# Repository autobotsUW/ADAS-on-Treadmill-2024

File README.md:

# ADAS-on-Treadmill-2024

## The project
The University of Waterloo’s Real-time Embedded Systems Lab hosts an autonomous driving system operating radio-controlled (RC) cars on a treadmill. The aim of this project is to simulate Advanced Driver-Assistance Systems on RC cars. The cars move on a treadmill. A camera is placed above the system to detect both the position of the vehicles and obstacles. Obstacles can be studs, which move only on one axis, or balls. The cars maintain a position on the treadmill until an obstacle is detected. They must then move to avoid it. 

Information from the camera is received on a PC and processed by ROS 2, before being transmitted to the cars via Bluetooth.  
We use ROS2 Humble with ubuntu 22.04

## How to launch
### Hardware

Place the cars at the front of the conveyor belt, at the edge of the empty space, with the batteries connected.  
Check that the camera is connected.

### Software

Oh to launch car controller:
```
cd ADAS-on-Treadmill-2024
cd ros2_jf_waterloo
source install/setup.bash
colcon build
cd launch
ros2 launch <launch_file>
```
Remember to check that each car is connected. (This is noted in the terminal and the Bluetooth modules flash intermittently).  

To launch the treadmill: use treadmill_control.py.  
Run the program, a window opens, you choose the speed and click on start.  
If nothing happens, set the enp9s0 Ethernet link to profile 2 with IP 192.168.124.1. 

# Package

## Nodes

### controller_node
- **Description**: The main node responsible for defining commands for the car. It allows changing algorithms to test different car behaviors.

### camera_node
- **Description**: This node captures images from the camera and provides the position of the cars and obstacles.

### camera_with_apriltags_node
- **Description**: This node captures images from the camera and provides the position of the cars and obstacles with apriltags to separate the cars.

### bluetooth_node
- **Description**: This node sends commands to the car via Bluetooth.

### input_node
- **Description**: This node receives user inputs to change the car's position.

### display_node
- **Description**: This node displays the position of the cars and obstacles.

### avoiding_obstacles_node
- **Description**: This node defines input positions to avoid obstacles.

### treadmill_control_node
- **Description**: This node controls the treadmill.

### security_node
- **Description**: This node detects anomalies.

### save_topic
- **Description**: This node saves data in several topics in a CSV file.

## Topics

To allow communication between these nodes, several topics are used:

### /car_position
- **Type**: Int32 list
- **Description**: List of car positions and their dimensions.
- **Format**: `[id_1, x_1, y_1, \theta_1, height_1, width_1, id_2, x_2, y_2, \theta_2, height_2, width_2, ...]`

### /input_position
- **Type**: Int32 list
- **Description**: User input positions.
- **Format**: `[id_1, X_input1, Y_input1, id_2, X_input2, Y_input2, ...]`

### /command
- **Type**: Int32 list
- **Description**: Speed and angle commands for the car.
- **Format**: `[id_1, speed_1, angle_1, id_2, speed_2, angle_2, ...]`

### /obstacles_position
- **Type**: Int32 list
- **Description**: Position of obstacles.
- **Format**: `[x_1, y_1, radius_1, x_2, y_2, radius_2, ...]`

### /error
- **Type**: String
- **Description**: Error messages.

### /treadmill
- **Type**: String
- **Description**: Commands for the treadmill.

## Launch files:
- **ADAS_on_treadmill_launch**: one car go to the position that you define.
- **ADAS_on_treadmill_launch_with_obstacles**: one car avoid obstacles.
- **ADAS_on_treadmill_launch_several_cars**: the car avoid obstacles for several cars. Works for one car
- **ADAS_on_treadmill_launch_road**: highway simulation with lane change

## Contact:
For any information, you can contact us at:  
jules.farnault@ens-paris-saclay.fr  
zambelli.lucas2@gmail.com

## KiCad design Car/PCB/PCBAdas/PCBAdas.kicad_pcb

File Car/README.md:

# Car
For this project, we'll be using two Latrax RC cars. We'll be keeping only the mechanical parts, the DC motor and servomotor.  
To control the car, we'll use an arduino Uno. To control the motor, we'll use a PWM-controlled IRLZ34N MOSFET.  
Bluetooth connection with the computer is via the HC05 module.  
To protect the Arduino, we'll use a pull-up resistor and a flyback diode.

## Possible operating problems :
If the static error is too high for one of the cars, it's best to redefine the servo center. To do this, run the program with only the problem car on the treadmill and modify the “center_servo” variable associated with the car id in the “control-node” node. 

## Electrical Circuit:

## Problems encountered:
Our main problem is noise on the servomotor.  
We tested the system with an Arduino Uno board and a Raspberry Pi Pico W. We noticed that the PWM generated by the Raspberry Pico was less stable than that generated by the Arduino, and therefore accentuated the noise phenomenon on the servo motor.  
To reduce the amplitude of the noise, we decided to supply the servo motor with 5V.  
To generate the PWM that controls the motor, we found that it was more efficient to generate it manually, using the writeMicroseconds function rather than the Library Arduino Servo.

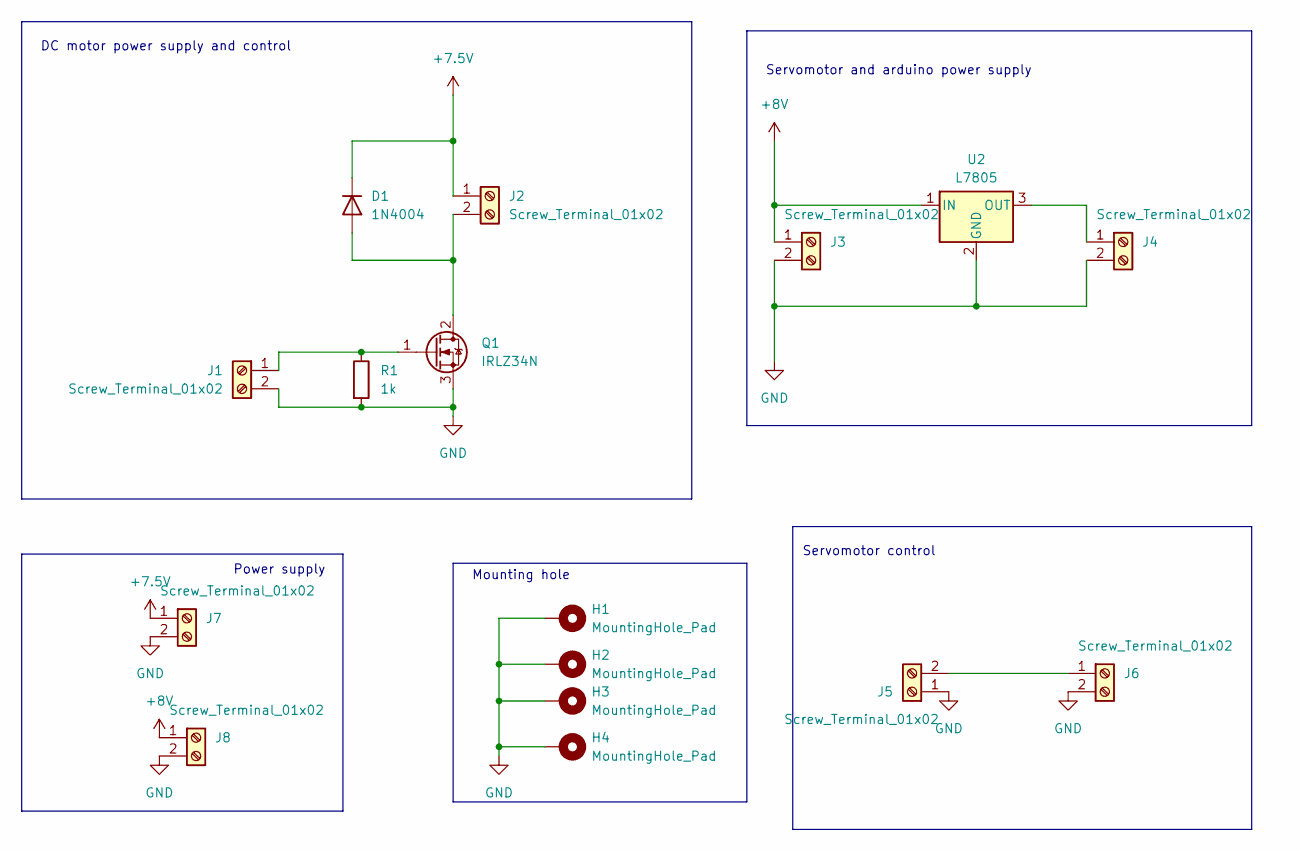
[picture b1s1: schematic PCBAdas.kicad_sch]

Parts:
D1: 1N4004; D_DO-41_SOD81_P10.16mm_Horizontal
H1, H2, H3, H4: MountingHole_Pad; MountingHole_3.2mm_M3_DIN965_Pad
J1, J2, J3, J4, J5, J6, J7, J8: Screw_Terminal_01x02; CONN_TB002-500-02BE_CUD
Q1: IRLZ34N; TO-220-3_Vertical
R1: 1k; R_Axial_DIN0207_L6.3mm_D2.5mm_P7.62mm_Horizontal
U2: L7805; TO254P460X1020X1945-3P

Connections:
+7.5V: D1.1 (K), J2.1, J7.1
+8V: J3.1, J8.1, U2.1 (IN)
GND: H1.1, H2.1, H3.1, H4.1, J1.2, J3.2, J4.2, J5.1, J6.2, J7.2, J8.2, Q1.3 (S), R1.2, U2.2 (GND)
unnamed: D1.2 (A), J2.2, Q1.2 (D)
unnamed: J1.1, Q1.1 (G), R1.1
unnamed: J4.1, U2.3 (OUT)
unnamed: J5.2, J6.1

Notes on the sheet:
Servomotor control
DC motor power supply and control
Power supply
Mounting hole
Servomotor and arduino power supply

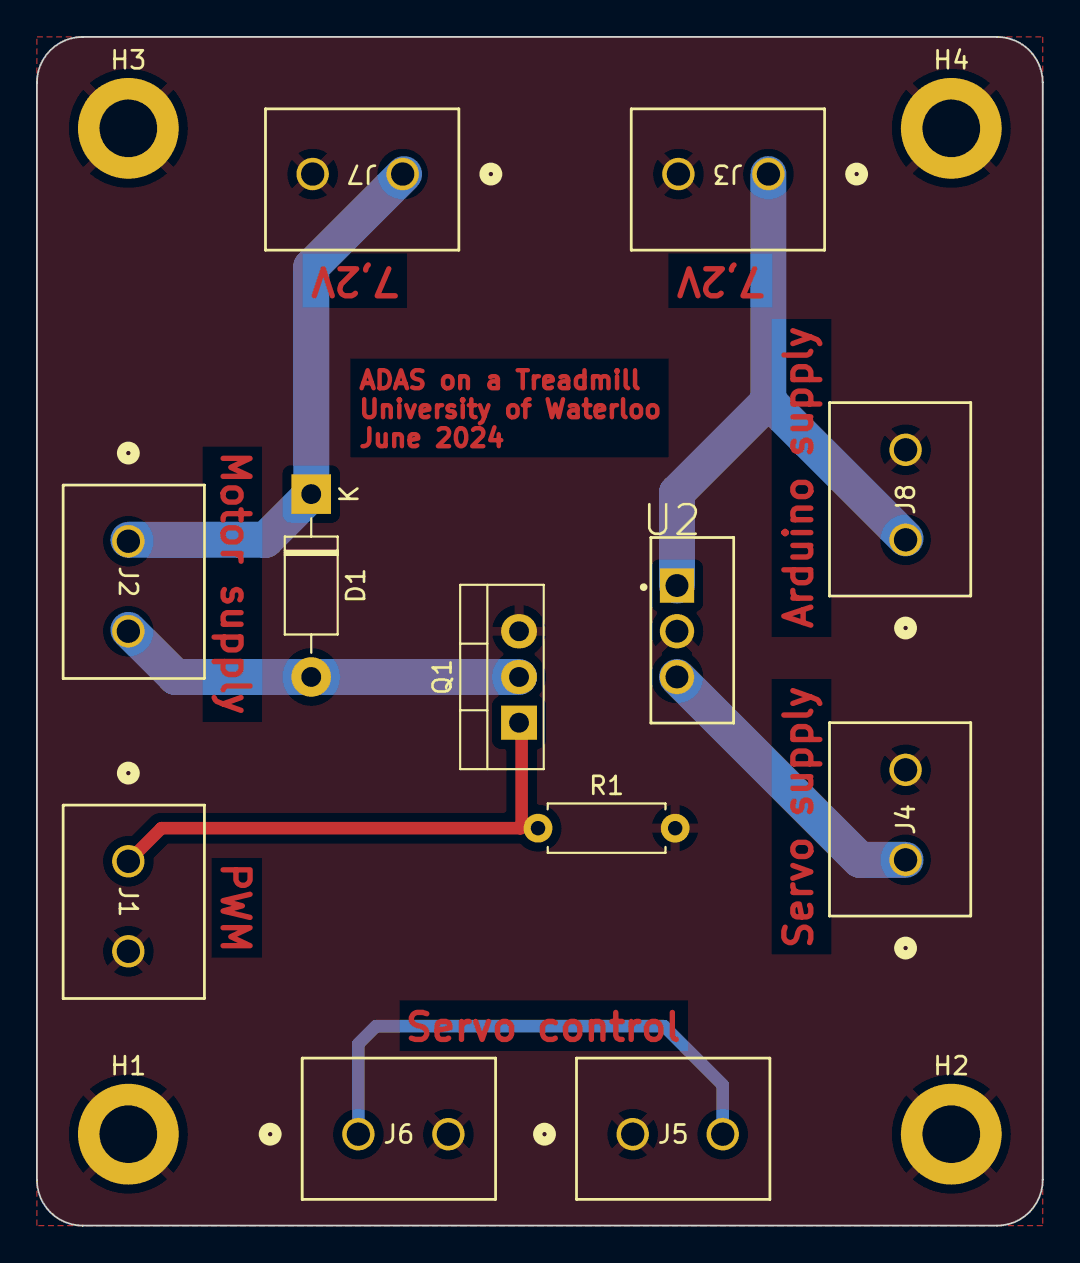
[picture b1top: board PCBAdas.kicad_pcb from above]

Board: 2 copper layers, 55.9 x 66.0 mm, 16 parts (0 on the bottom side), 7 nets.

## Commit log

2024-06-10 test
2024-06-10 first commit add gitignore for log build and insatll
2024-06-10 add site
2024-06-10 add car folder
2024-06-10 create a folder
2024-06-10 create a folder for the treadmill
2024-06-10 test parameters
2024-06-10 security_node
2024-06-10 modifications
2024-06-10 value
2024-06-11 stanley controller
2024-06-12 commentaire
2024-06-12 comment
2024-06-12 Rename Untitled Sketch 2_bb.png to ArduinoCircuit.png
2024-06-12 add comment
2024-06-12 change theme of site
2024-06-13 create tools
2024-06-13 add tools
2024-06-13 tags
2024-06-14 apriltags
2024-06-14 apriltags detector
2024-06-14 code apriltags
2024-06-17 add others bluetooth module
2024-06-17 modification to control several cars
2024-06-18 avoid obstacles for several cars
2024-06-19 correction bugs
2024-06-20 new mesure
2024-06-21 bugs
2024-06-24 security
2024-06-24 test camera IR ximea
2024-06-25 2 cars
2024-06-26 SMVector documentation
2024-06-26 april tags use
2024-06-26 new picture
2024-06-26 new mesure with 2 cars
2024-06-26 change methods to mesure data
2024-06-26 change Xmin
2024-06-26 new folders
2024-06-27 test 2 cars
2024-06-27 display data
2024-06-27 change treadmill program
2024-06-27 add readme
2024-06-28 modification to plot data
2024-06-28 picture
2024-06-28 treadmill control
2024-07-02 new node
2024-07-02 add anomalies
2024-07-02 actualize picture
2024-07-05 several test
2024-07-09 add lane in the treadmill
2024-07-09 add lanes on the treadmill
2024-07-10 add road control
2024-07-10 car on road
2024-07-11 mouvment
2024-07-15 Rename _readme.md to &readme.md
2024-07-15 avoid obstacles with road
2024-07-16 Rename &readme.md to README.md
2024-07-22 trust score create
2024-07-22 screen
2024-07-24 modification readme
2024-07-24 readme
2024-07-24 rosbag
2024-07-25 add STL test
2024-07-25 create STL node
2024-07-25 data
2024-07-26 svg to png
2024-07-28 Created YOLOv10_Integration Folder
    Will be used to add the dataset and ROS node integration with YOLO for object detection
2024-07-29 new data
2024-07-29 new tracer_data3cars_with_obstacles
2024-07-29 plot 3 cars
2024-07-29 new plot
2024-07-29 plot video
2024-07-30 delete
2024-07-30 stl programm
2024-07-31 stl node
2024-07-31 add screen
2024-08-01 new STL mesure
2024-08-02 YOLO test
2024-08-02 add yolo
2024-08-02 rename
2024-08-06 input with trust score
